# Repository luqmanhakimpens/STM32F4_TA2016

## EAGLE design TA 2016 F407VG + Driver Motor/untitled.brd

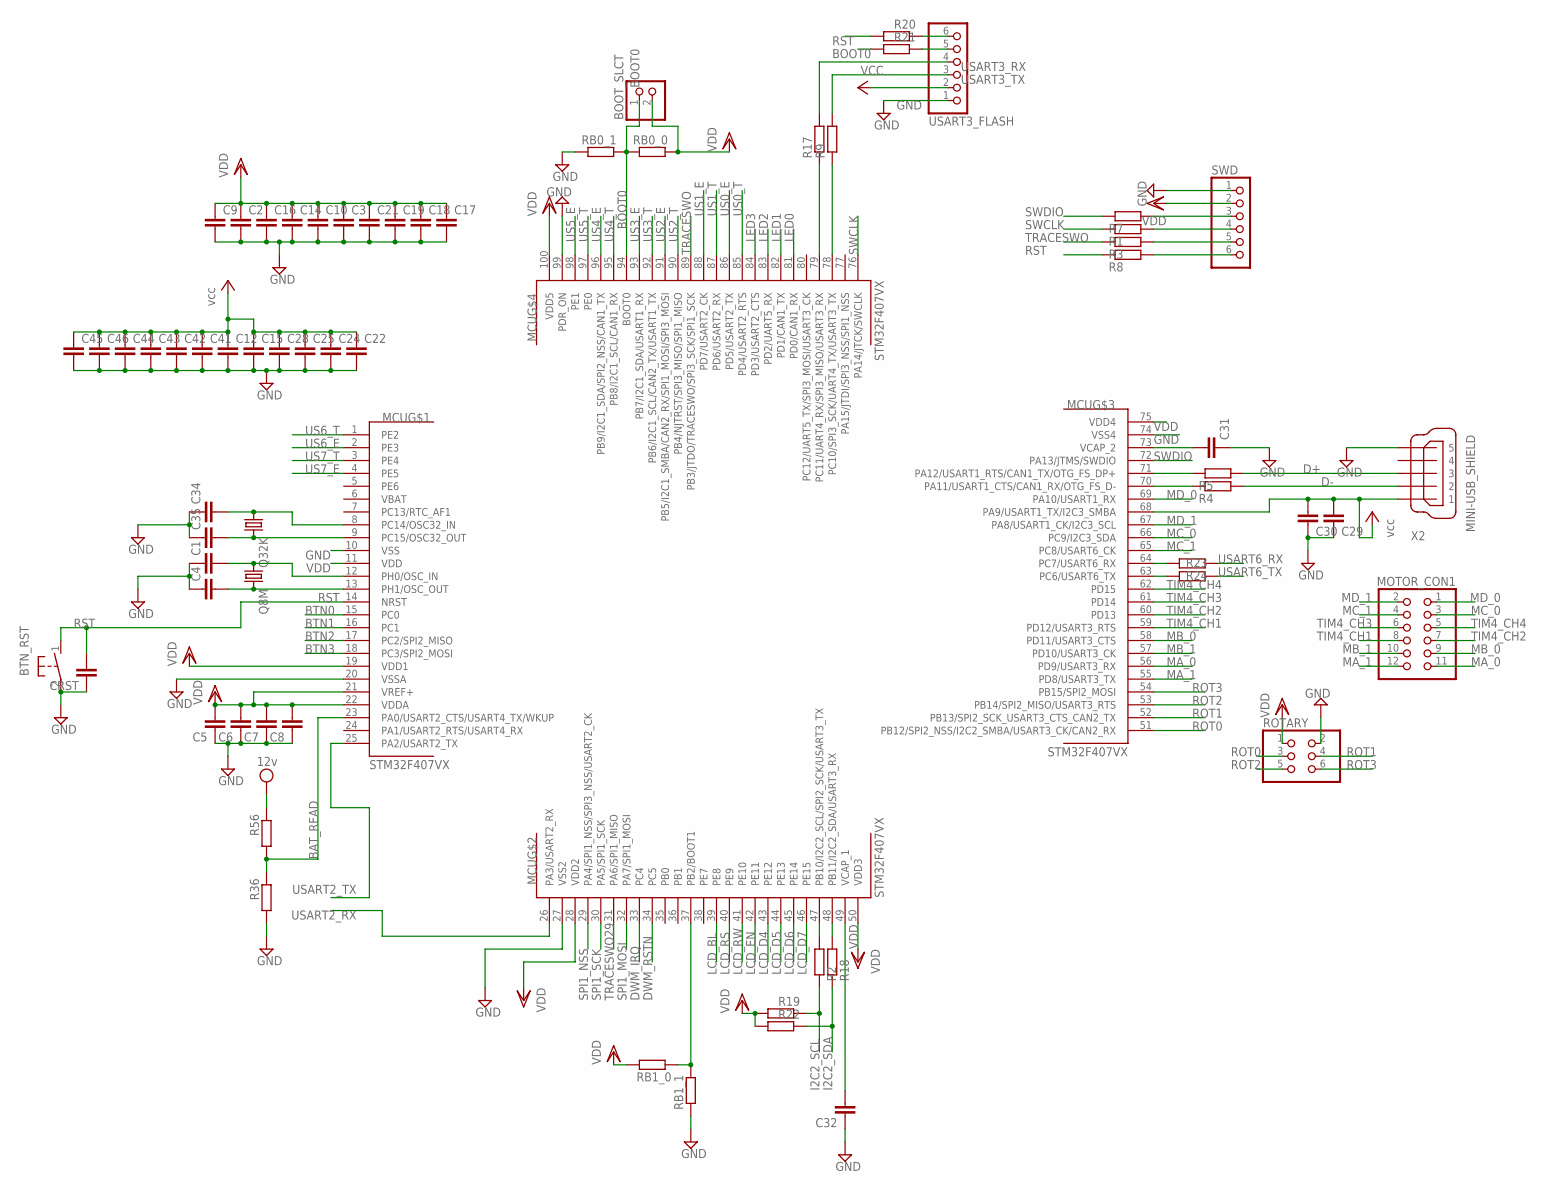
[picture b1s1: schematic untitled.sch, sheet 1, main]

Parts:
BOOT_SLCT: PINHD-1X2; 1X02
BTN_RST: PUSHBTN; PUSHBUTTON
C1, C2, C3, C4, C5, C6, C7, C8, C9, C10, C12, C14, C15, C16, C17, C18, C19, C21, C22, C24, C25, C28, C29, C30, C31, C32, C34, C35, C41, C42, C43, C44, C45, C46: C-EUC0805; C0805
CRST: C-EUC0805; C0805
MCU: STM32F407VX; LQFP100
MOTOR_CON1: PINHD-2X6; 2X06
Q8M: CRYSTALHC49U-V; HC49U-V
Q32K: CRYSTALTC26V; TC26V
R1, R2, R3, R4, R5, R7, R8, R9, R17, R18, R19, R22, R23, R24, R36, R56: R-EU_M0805; M0805
R20, R21: R-EU_R0805; R0805
RB0_0, RB0_1, RB1_0, RB1_1: R-EU_M0805; M0805
ROTARY: PINHD-2X3; 2X03
SWD: PINHD-1X06_2.54-S; 1X06-S
USART3_FLASH: PINHD-1X6; 1X06
X2: MINI-USB_SHIELD; 32005-400

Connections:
12V: R56.1; also elsewhere on the board
BAT_READ: MCU.23 (PA0/USART2_CTS/USART4_TX/WKUP), R36.1, R56.2
BOOT0: BOOT_SLCT.1, MCU.94 (BOOT0), R21.2, RB0_0.1, RB0_1.2
BOOT1: MCU.37 (PB2/BOOT1), RB1_0.1, RB1_1.2
BTN0: MCU.15 (PC0); also elsewhere on the board
BTN1: MCU.16 (PC1); also elsewhere on the board
BTN2: MCU.17 (PC2/SPI2_MISO); also elsewhere on the board
BTN3: MCU.18 (PC3/SPI2_MOSI); also elsewhere on the board
D+: R5.2, X2.3
D-: R4.2, X2.2
DWM_IRQ: MCU.33 (PC4); also elsewhere on the board
DWM_RSTN: MCU.34 (PC5); also elsewhere on the board
GND: BTN_RST.2, C1.1, C2.2, C3.2, C4.1, C5.1, C6.1, C7.1, C8.1, C9.2, C10.2, C12.2, C14.2, C15.2, C16.2, C17.2, C18.2, C19.2, C21.2, C22.2, C24.2, C25.2, C28.2, C29.1, C30.1, C31.1, C32.1, C34.1, C35.1, C41.2, C42.2, C43.2, C44.2, C45.2, C46.2, CRST.1, MCU.10 (VSS), MCU.20 (VSSA), MCU.27 (VSS2), MCU.74 (VSS4), MCU.99 (PDR_ON), R36.2, RB0_1.1, RB1_1.1, ROTARY.2, SWD.1, USART3_FLASH.1, X2.5; also elsewhere on the board
I2C2_SCL: R2.1, R19.1; also elsewhere on the board
I2C2_SDA: R18.1, R22.1; also elsewhere on the board
LCD_BL: MCU.39 (PE8); also elsewhere on the board
LCD_D4: MCU.43 (PE12); also elsewhere on the board
LCD_D5: MCU.44 (PE13); also elsewhere on the board
LCD_D6: MCU.45 (PE14); also elsewhere on the board
LCD_D7: MCU.46 (PE15); also elsewhere on the board
LCD_EN: MCU.42 (PE11); also elsewhere on the board
LCD_RS: MCU.40 (PE9); also elsewhere on the board
LCD_RW: MCU.41 (PE10); also elsewhere on the board
LED0: MCU.81 (PD0/CAN1_RX); also elsewhere on the board
LED1: MCU.82 (PD1/CAN1_TX); also elsewhere on the board
LED2: MCU.83 (PD2/UART5_RX); also elsewhere on the board
LED3: MCU.84 (PD3/USART2_CTS); also elsewhere on the board
MA_0: MCU.56 (PD9/USART3_RX), MOTOR_CON1.11
MA_1: MCU.55 (PD8/USART3_TX), MOTOR_CON1.12
MB_0: MCU.58 (PD11/USART3_CTS), MOTOR_CON1.9
MB_1: MCU.57 (PD10/USART3_CK), MOTOR_CON1.10
MC_0: MCU.66 (PC9/I2C3_SDA), MOTOR_CON1.3
MC_1: MCU.65 (PC8/USART6_CK), MOTOR_CON1.4
MD_0: MCU.69 (PA10/USART1_RX), MOTOR_CON1.1
MD_1: MCU.67 (PA8/USART1_CK/I2C3_SCL), MOTOR_CON1.2
unnamed: MCU.64 (PC7/USART6_RX), R23.1
unnamed: R3.2, SWD.5
unnamed: C31.2, MCU.73 (VCAP_2)
unnamed: MCU.63 (PC6/USART6_TX), R24.1
unnamed: R8.2, SWD.6
unnamed: R7.2, SWD.3
unnamed: R1.2, SWD.4
unnamed: MCU.47 (PB10/I2C2_SCL/SPI2_SCK/USART3_TX), R2.2
unnamed: C32.2, MCU.49 (VCAP_1)
unnamed: MCU.48 (PB11/I2C2_SDA/USART3_RX), R18.2
unnamed: R20.1, USART3_FLASH.6
unnamed: MCU.78 (PC10/SPI3_SCK/UART4_TX/USART3_TX), R9.1
unnamed: MCU.79 (PC11/UART4_RX/SPI3_MISO/USART3_RX), R17.1
unnamed: R21.1, USART3_FLASH.5
unnamed: MCU.71 (PA12/USART1_RTS/CAN1_TX/OTG_FS_DP+), R5.1
unnamed: MCU.70 (PA11/USART1_CTS/CAN1_RX/OTG_FS_D-), R4.1
OSC32_IN1: C34.2, MCU.8 (PC14/OSC32_IN), Q32K.1
OSC32_OUT1: C35.2, MCU.9 (PC15/OSC32_OUT), Q32K.2
OSC_IN: C1.2, MCU.12 (PH0/OSC_IN), Q8M.1
OSC_OUT: C4.2, MCU.13 (PH1/OSC_OUT), Q8M.2
ROT0: MCU.51 (PB12/SPI2_NSS/I2C2_SMBA/USART3_CK/CAN2_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), ROTARY.3
ROT1: MCU.52 (PB13/SPI2_SCK_USART3_CTS_CAN2_TX), ROTARY.4
ROT2: MCU.53 (PB14/SPI2_MISO/USART3_RTS), ROTARY.5
ROT3: MCU.54 (PB15/SPI2_MOSI), ROTARY.6
RST: BTN_RST.1, CRST.2, MCU.14 (NRST), R8.1, R20.2
SPI1_MOSI: MCU.32 (PA7/SPI1_MOSI); also elsewhere on the board
SPI1_NSS: MCU.29 (PA4/SPI1_NSS/SPI3_NSS/USART2_CK); also elsewhere on the board
SPI1_SCK: MCU.30 (PA5/SPI1_SCK); also elsewhere on the board
SWCLK: MCU.76 (PA14/JTCK/SWCLK), R1.1
SWDIO: MCU.72 (PA13/JTMS/SWDIO), R7.1
TIM4_CH1: MCU.59 (PD12/USART3_RTS), MOTOR_CON1.8
TIM4_CH2: MCU.60 (PD13), MOTOR_CON1.7
TIM4_CH3: MCU.61 (PD14), MOTOR_CON1.6
TIM4_CH4: MCU.62 (PD15), MOTOR_CON1.5
TRACESWO: MCU.89 (PB3/JTDO/TRACESWO/SPI3_SCK/SPI1_SCK), R3.1
TRACESWO29: MCU.31 (PA6/SPI1_MISO); also elsewhere on the board
US0_E: MCU.86 (PD5/USART2_TX); also elsewhere on the board
US0_T: MCU.85 (PD4/USART2_RTS); also elsewhere on the board
US1_E: MCU.88 (PD7/USART2_CK); also elsewhere on the board
US1_T: MCU.87 (PD6/USART2_RX); also elsewhere on the board
US2_E: MCU.91 (PB5/I2C1_SMBA/CAN2_RX/SPI1_MOSI/SPI3_MO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); also elsewhere on the board
US2_T: MCU.90 (PB4/NJTRST/SPI3_MISO/SPI1_MISO); also elsewhere on the board
US3_E: MCU.93 (PB7/I2C1_SDA/USART1_RX); also elsewhere on the board
US3_T: MCU.92 (PB6/I2C1_SCL/CAN2_TX/USART1_TX); also elsewhere on the board
US4_E: MCU.96 (PB9/I2C1_SDA/SPI2_NSS/CAN1_TX); also elsewhere on the board
US4_T: MCU.95 (PB8/I2C1_SCL/CAN1_RX); also elsewhere on the board
US5_E: MCU.98 (PE1); also elsewhere on the board
US5_T: MCU.97 (PE0); also elsewhere on the board
US6_E: MCU.2 (PE3); also elsewhere on the board
US6_T: MCU.1 (PE2); also elsewhere on the board
US7_E: MCU.4 (PE5); also elsewhere on the board
US7_T: MCU.3 (PE4); also elsewhere on the board
USART2_RX: MCU.26 (PA3/USART2_RX); also elsewhere on the board
USART2_TX: MCU.25 (PA2/USART2_TX); also elsewhere on the board
USART3_RX: R17.2, USART3_FLASH.4; also elsewhere on the board
USART3_TX: R9.2, USART3_FLASH.3; also elsewhere on the board
USART6_RX: R23.2; also elsewhere on the board
USART6_TX: R24.2; also elsewhere on the board
VCC: C12.1, C15.1, C22.1, C24.1, C25.1, C28.1, C29.2, C30.2, C41.1, C42.1, C43.1, C44.1, C45.1, C46.1, MCU.68 (PA9/USART1_TX/I2C3_SMBA), USART3_FLASH.2, X2.1; also elsewhere on the board
VDD: BOOT_SLCT.2, C2.1, C3.1, C5.2, C6.2, C7.2, C8.2, C9.1, C10.1, C14.1, C16.1, C17.1, C18.1, C19.1, C21.1, MCU.11 (VDD), MCU.19 (VDD1), MCU.21 (VREF+), MCU.22 (VDDA), MCU.28 (VDD2), MCU.50 (VDD3), MCU.75 (VDD4), MCU.100 (VDD5), R19.2, R22.2, RB0_0.2, RB1_0.2, ROTARY.1, SWD.2; also elsewhere on the board

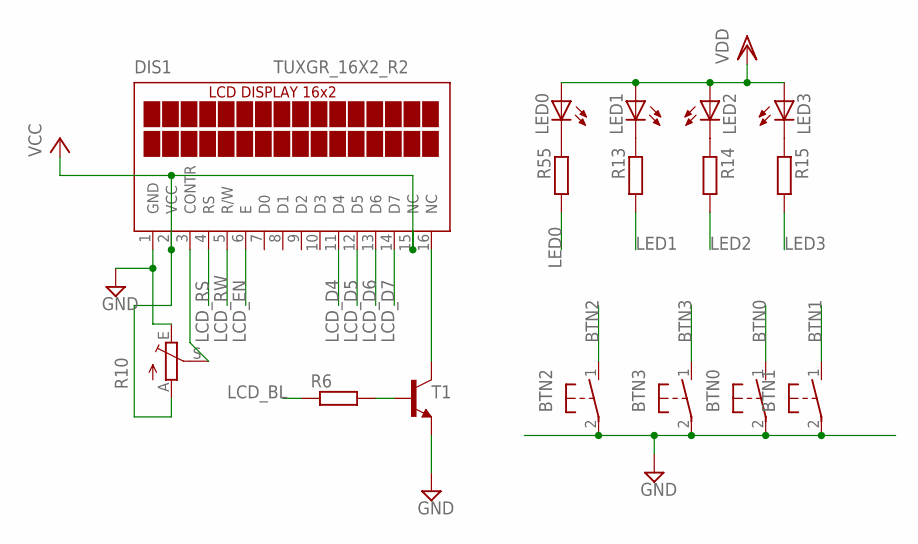
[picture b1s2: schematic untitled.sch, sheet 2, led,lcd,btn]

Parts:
BTN0, BTN1, BTN2, BTN3: PUSHBTN; PUSHBUTTON
DIS1: TUXGR_16X2_R2
LED0, LED1, LED2, LED3: LEDSMT1206; 1206
R6, R13, R14, R15, R55: R-EU_M0805; M0805
R10: TRIM_EU-CA6V; CA6V
T1: BC818-NPN-SOT23-BEC; SOT23-BEC

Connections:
BTN0: BTN0.1; also elsewhere on the board
BTN1: BTN1.1; also elsewhere on the board
BTN2: BTN2.1; also elsewhere on the board
BTN3: BTN3.1; also elsewhere on the board
GND: BTN0.2, BTN1.2, BTN2.2, BTN3.2, DIS1.1 (GND), R10.E, T1.E; also elsewhere on the board
LCD_BL: R6.1; also elsewhere on the board
LCD_D4: DIS1.11 (D4); also elsewhere on the board
LCD_D5: DIS1.12 (D5); also elsewhere on the board
LCD_D6: DIS1.13 (D6); also elsewhere on the board
LCD_D7: DIS1.14 (D7); also elsewhere on the board
LCD_EN: DIS1.6 (E); also elsewhere on the board
LCD_RS: DIS1.4 (RS); also elsewhere on the board
LCD_RW: DIS1.5 (R/W); also elsewhere on the board
LED0: R55.2; also elsewhere on the board
LED1: R13.2; also elsewhere on the board
LED2: R14.2; also elsewhere on the board
LED3: R15.2; also elsewhere on the board
unnamed: DIS1.3 (CONTR), R10.S
unnamed: LED1.C, R13.1
unnamed: LED2.C, R14.1
unnamed: LED3.C, R15.1
unnamed: R6.2, T1.B
unnamed: DIS1.16 (NC), T1.C
unnamed: LED0.C, R55.1
VCC: DIS1.2 (VCC), DIS1.15 (NC), R10.A; also elsewhere on the board
VDD: LED0.A, LED1.A, LED2.A, LED3.A; also elsewhere on the board

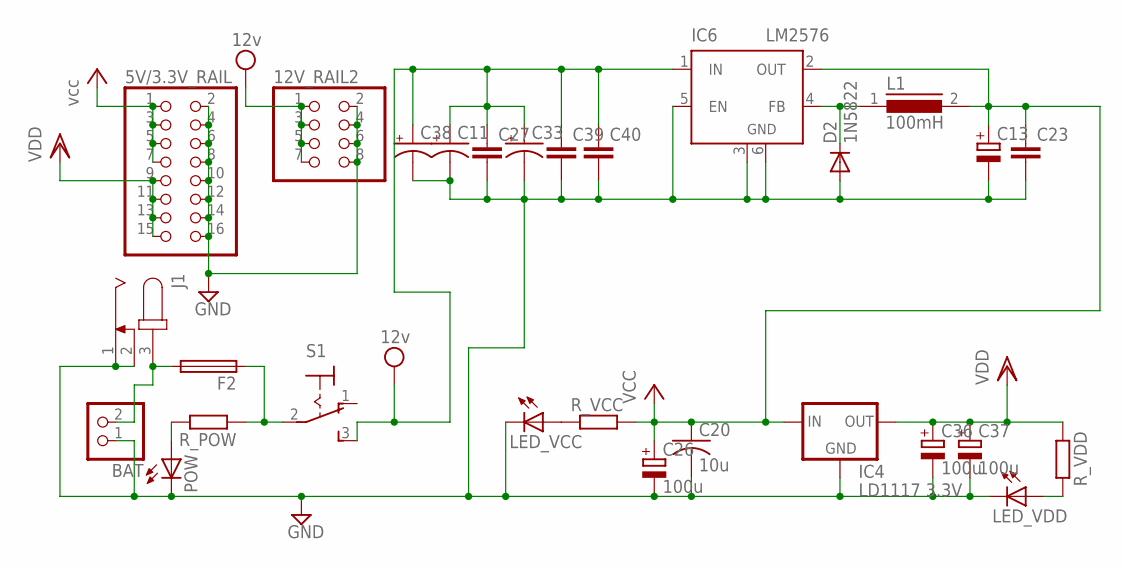
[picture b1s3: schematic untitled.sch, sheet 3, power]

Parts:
5V/3.3V_RAIL: PINHD-2X8; 2X08
12V_RAIL2: PINHD-2X4; 2X04
BAT: PINHD-1X2; 1X02
C11, C33, C38: CAP_POLH13; PANASONIC_H13
C13: CPOL-EU153CLV-1012; 153CLV-1012
C20: 10u; C0805
C23, C27, C39, C40: C-EUC0805; C0805
C26, C36, C37: 100u; 153CLV-1012
D2: 1N5822; DO15-12
F2: FUSESHK20L; SHK20L
IC4: LD1117 3.3V; SOT223
IC6: LM2576; TO263-5
J1: JACK-PLUG1; SPC4078
L1: 100mH; DR127
LED_VCC: LEDSMT1206; 1206
LED_VDD: LEDSMT1206; 1206
POW: LEDSMT1206; 1206
R_POW: R-EU_M0805; M0805
R_VCC: R-EU_M0805; M0805
R_VDD: R-EU_M0805; M0805
S1: 320-916

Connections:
12V: 12V_RAIL2.1, 12V_RAIL2.3, 12V_RAIL2.5, 12V_RAIL2.7, C11.+, C27.1, C33.+, C38.+, C39.1, C40.1, IC6.1 (IN), S1.3 (S); also elsewhere on the board
GND: 5V/3.3V_RAIL.2, 5V/3.3V_RAIL.4, 5V/3.3V_RAIL.6, 5V/3.3V_RAIL.8, 5V/3.3V_RAIL.10, 5V/3.3V_RAIL.12, 5V/3.3V_RAIL.14, 5V/3.3V_RAIL.16, 12V_RAIL2.2, 12V_RAIL2.4, 12V_RAIL2.6, 12V_RAIL2.8, BAT.1, C11.-, C13.-, C20.2, C23.2, C26.-, C27.2, C33.-, C36.-, C37.-, C38.-, C39.2, C40.2, D2.A, IC4.1 (GND), IC6.3 (GND), IC6.5 (EN), IC6.6 (GND), J1.1, J1.2, LED_VCC.C, LED_VDD.C, POW.C; also elsewhere on the board
unnamed: BAT.2, F2.2A (2), J1.3
unnamed: LED_VDD.A, R_VDD.2
unnamed: D2.C, IC6.4 (FB), L1.1
unnamed: POW.A, R_POW.2
unnamed: LED_VCC.A, R_VCC.1
unnamed: F2.1A (1), R_POW.1, S1.2
VCC: 5V/3.3V_RAIL.1, 5V/3.3V_RAIL.3, 5V/3.3V_RAIL.5, 5V/3.3V_RAIL.7, C13.+, C20.1, C23.1, C26.+, IC4.3 (IN), IC6.2 (OUT), L1.2, R_VCC.2; also elsewhere on the board
VDD: 5V/3.3V_RAIL.9, 5V/3.3V_RAIL.11, 5V/3.3V_RAIL.13, 5V/3.3V_RAIL.15, C36.+, C37.+, IC4.2 (OUT), R_VDD.1; also elsewhere on the board

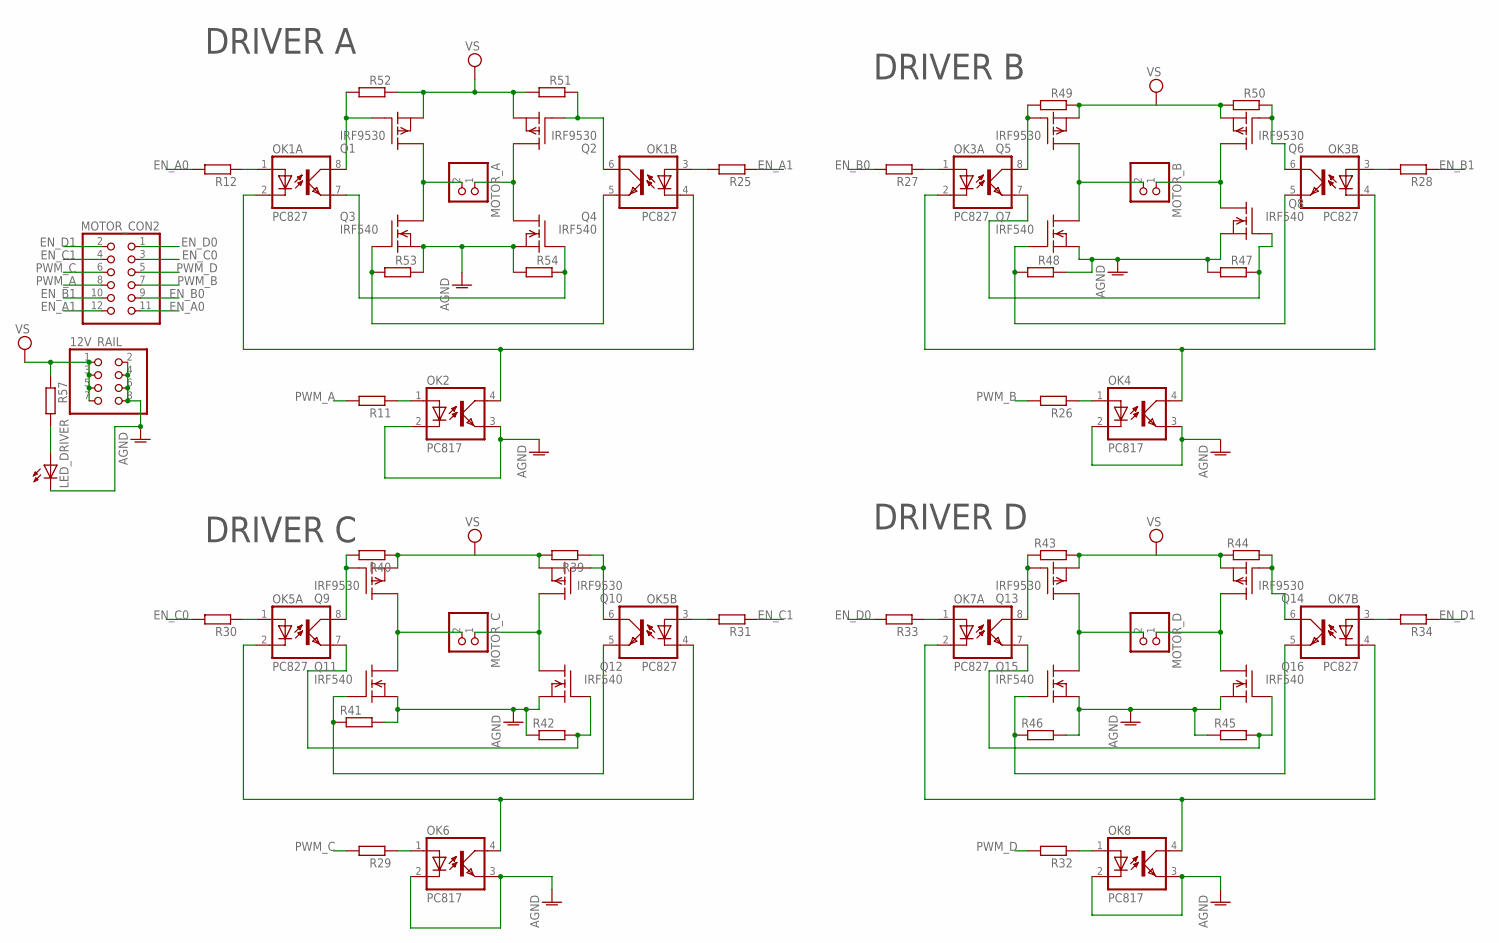
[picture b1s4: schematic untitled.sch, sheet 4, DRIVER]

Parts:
12V_RAIL: PINHD-2X4; 2X04
LED_DRIVER: LEDSMT1206; 1206
MOTOR_A: PINHD-1X2/90; 1X02/90
MOTOR_B: PINHD-1X2/90; 1X02/90
MOTOR_C: PINHD-1X2/90; 1X02/90
MOTOR_CON2: PINHD-2X6; 2X06
MOTOR_D: PINHD-1X2/90; 1X02/90
OK1, OK3, OK5, OK7: PC827; DIL08
OK2, OK4, OK6, OK8: PC817; DIL04
Q1, Q2, Q5, Q6, Q9, Q10, Q13, Q14: IRF9530; TO220
Q3, Q4, Q7, Q8, Q11, Q12, Q15, Q16: IRF540; TO220
R11, R12, R25, R26, R27, R28, R29, R30, R31, R32, R33, R34, R39, R40, R41, R42, R43, R44, R45, R46, R47, R48, R49, R50, R51, R52, R53, R54, R57: R-EU_M0805; M0805

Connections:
AGND: 12V_RAIL.2, 12V_RAIL.4, 12V_RAIL.6, 12V_RAIL.8, LED_DRIVER.C, OK2.2 (C), OK2.3 (EMIT), OK4.2 (C), OK4.3 (EMIT), OK6.2 (C), OK6.3 (EMIT), OK8.2 (C), OK8.3 (EMIT), Q3.3 (S), Q4.3 (S), Q7.3 (S), Q8.3 (S), Q11.3 (S), Q12.3 (S), Q15.3 (S), Q16.3 (S), R41.2, R42.1, R45.1, R46.2, R47.2, R48.1, R53.1, R54.2
EN_A0: MOTOR_CON2.11, R12.2
EN_A1: MOTOR_CON2.12, R25.1
EN_B0: MOTOR_CON2.9, R27.2
EN_B1: MOTOR_CON2.10, R28.1
EN_C0: MOTOR_CON2.3, R30.2
EN_C1: MOTOR_CON2.4, R31.1
EN_D0: MOTOR_CON2.1, R33.2
EN_D1: MOTOR_CON2.2, R34.1
unnamed: OK3.7 (EMIT), Q8.1 (G), R47.1
unnamed: MOTOR_A.2, Q1.2 (D), Q3.2 (D)
unnamed: MOTOR_A.1, Q2.2 (D), Q4.2 (D)
unnamed: OK1.8 (COL), Q1.1 (G), R52.2
unnamed: OK1.7 (EMIT), Q4.1 (G), R54.1
unnamed: OK1.6 (COL), Q2.1 (G), R51.1
unnamed: OK1.5 (EMIT), Q3.1 (G), R53.2
unnamed: OK1.2 (C), OK1.4 (C), OK2.4 (COL)
unnamed: MOTOR_B.2, Q5.2 (D), Q7.2 (D)
unnamed: MOTOR_B.1, Q6.2 (D), Q8.2 (D)
unnamed: OK1.1 (A), R12.1
unnamed: OK1.3 (A), R25.2
unnamed: OK3.8 (COL), Q5.1 (G), R49.2
unnamed: OK2.1 (A), R11.1
unnamed: OK3.6 (COL), Q6.1 (G), R50.1
unnamed: OK3.5 (EMIT), Q7.1 (G), R48.2
unnamed: OK3.2 (C), OK3.4 (C), OK4.4 (COL)
unnamed: OK3.1 (A), R27.1
unnamed: OK3.3 (A), R28.2
unnamed: OK4.1 (A), R26.1
unnamed: MOTOR_C.2, Q9.2 (D), Q11.2 (D)
unnamed: MOTOR_C.1, Q10.2 (D), Q12.2 (D)
unnamed: OK5.8 (COL), Q9.1 (G), R40.2
unnamed: OK5.7 (EMIT), Q12.1 (G), R42.2
unnamed: OK5.6 (COL), Q10.1 (G), R39.1
unnamed: OK5.5 (EMIT), Q11.1 (G), R41.1
unnamed: OK5.2 (C), OK5.4 (C), OK6.4 (COL)
unnamed: OK5.1 (A), R30.1
unnamed: OK5.3 (A), R31.2
unnamed: OK6.1 (A), R29.1
unnamed: MOTOR_D.2, Q13.2 (D), Q15.2 (D)
unnamed: MOTOR_D.1, Q14.2 (D), Q16.2 (D)
unnamed: OK7.8 (COL), Q13.1 (G), R43.1
unnamed: OK7.7 (EMIT), Q16.1 (G), R45.2
unnamed: OK7.6 (COL), Q14.1 (G), R44.2
unnamed: OK7.5 (EMIT), Q15.1 (G), R46.1
unnamed: OK7.2 (C), OK7.4 (C), OK8.4 (COL)
unnamed: OK7.1 (A), R33.1
unnamed: OK7.3 (A), R34.2
unnamed: OK8.1 (A), R32.1
unnamed: LED_DRIVER.A, R57.2
PWM_A: MOTOR_CON2.8, R11.2
PWM_B: MOTOR_CON2.7, R26.2
PWM_C: MOTOR_CON2.6, R29.2
PWM_D: MOTOR_CON2.5, R32.2
VS+: 12V_RAIL.1, 12V_RAIL.3, 12V_RAIL.5, 12V_RAIL.7, Q1.3 (S), Q2.3 (S), Q5.3 (S), Q6.3 (S), Q9.3 (S), Q10.3 (S), Q13.3 (S), Q14.3 (S), R39.2, R40.1, R43.2, R44.1, R49.1, R50.2, R51.2, R52.1, R57.1

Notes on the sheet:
DRIVER A
DRIVER B
DRIVER C
DRIVER D

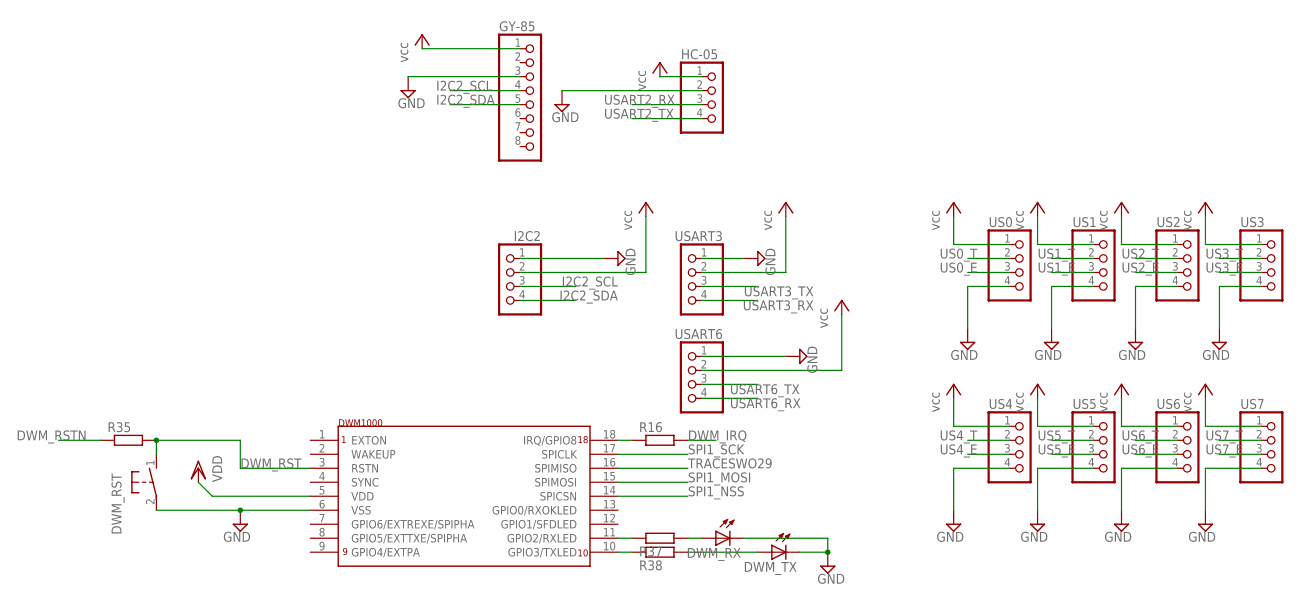
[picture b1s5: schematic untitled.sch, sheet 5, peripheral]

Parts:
DWM_RST: PUSHBTN; PUSHBUTTON
DWM_RX: LEDSMT1206; 1206
DWM_TX: LEDSMT1206; 1206
GY-85: PINHD-1X8; 1X08
HC-05: PINHD-1X4; 1X04
I2C2: PINHD-1X4; 1X04
R16, R35, R37, R38: R-EU_M0805; M0805
U$3: MY_DWM1000_PAD_ONLY
US0, US1, US2, US3, US4, US5, US6, US7: PINHD-1X4; 1X04
USART3, USART6: PINHD-1X4; 1X04

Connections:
DWM_IRQ: R16.2; also elsewhere on the board
DWM_RST: DWM_RST.1, R35.2, U$3.3 (RSTN)
DWM_RSTN: R35.1; also elsewhere on the board
GND: DWM_RST.2, DWM_RX.C, DWM_TX.C, GY-85.3, HC-05.2, I2C2.1, U$3.6 (VSS), US0.4, US1.4, US2.4, US3.4, US4.4, US5.4, US6.4, US7.4, USART3.1, USART6.1; also elsewhere on the board
I2C2_SCL: GY-85.4, I2C2.3; also elsewhere on the board
I2C2_SDA: GY-85.5, I2C2.4; also elsewhere on the board
unnamed: R37.1, U$3.11 (GPIO2/RXLED)
unnamed: R38.1, U$3.10 (GPIO3/TXLED)
unnamed: DWM_RX.A, R37.2
unnamed: DWM_TX.A, R38.2
unnamed: R16.1, U$3.18 (IRQ/GPIO8)
SPI1_MOSI: U$3.15 (SPIMOSI); also elsewhere on the board
SPI1_NSS: U$3.14 (SPICSN); also elsewhere on the board
SPI1_SCK: U$3.17 (SPICLK); also elsewhere on the board
TRACESWO29: U$3.16 (SPIMISO); also elsewhere on the board
US0_E: US0.3; also elsewhere on the board
US0_T: US0.2; also elsewhere on the board
US1_E: US1.3; also elsewhere on the board
US1_T: US1.2; also elsewhere on the board
US2_E: US2.3; also elsewhere on the board
US2_T: US2.2; also elsewhere on the board
US3_E: US3.3; also elsewhere on the board
US3_T: US3.2; also elsewhere on the board
US4_E: US4.3; also elsewhere on the board
US4_T: US4.2; also elsewhere on the board
US5_E: US5.3; also elsewhere on the board
US5_T: US5.2; also elsewhere on the board
US6_E: US6.3; also elsewhere on the board
US6_T: US6.2; also elsewhere on the board
US7_E: US7.3; also elsewhere on the board
US7_T: US7.2; also elsewhere on the board
USART2_RX: HC-05.3; also elsewhere on the board
USART2_TX: HC-05.4; also elsewhere on the board
USART3_RX: USART3.4; also elsewhere on the board
USART3_TX: USART3.3; also elsewhere on the board
USART6_RX: USART6.4; also elsewhere on the board
USART6_TX: USART6.3; also elsewhere on the board
VCC: GY-85.1, HC-05.1, I2C2.2, US0.1, US1.1, US2.1, US3.1, US4.1, US5.1, US6.1, US7.1, USART3.2, USART6.2; also elsewhere on the board
VDD: U$3.5 (VDD); also elsewhere on the board

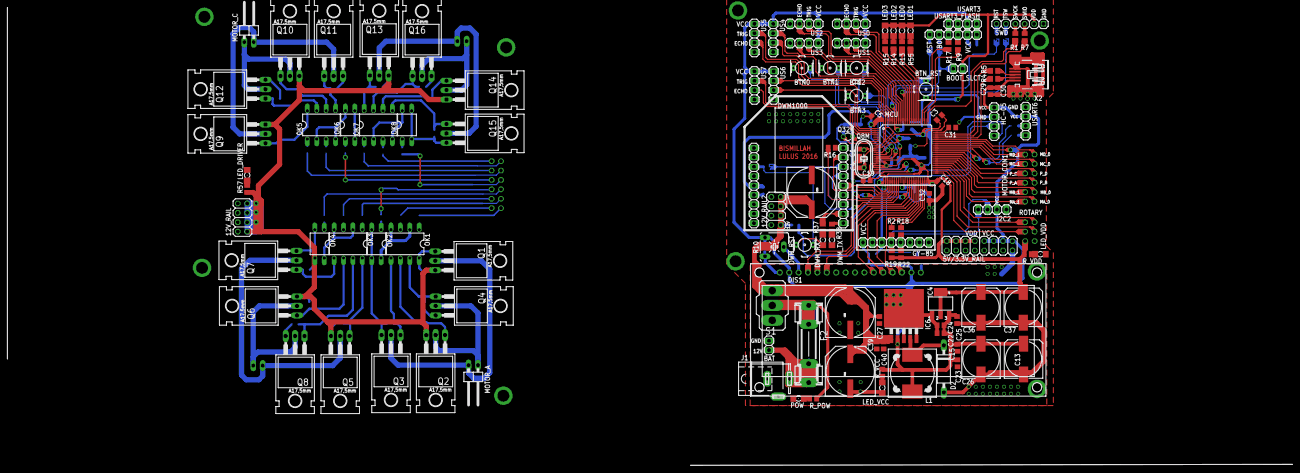
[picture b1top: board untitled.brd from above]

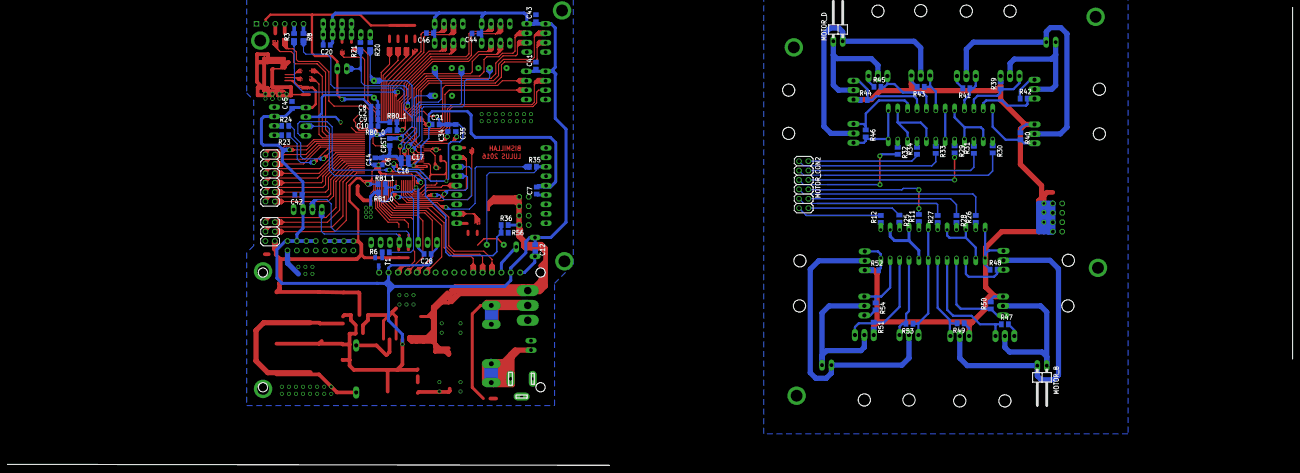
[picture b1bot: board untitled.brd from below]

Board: 2 copper layers, 347.2 x 123.7 mm, 192 parts (70 on the bottom side), 169 nets.

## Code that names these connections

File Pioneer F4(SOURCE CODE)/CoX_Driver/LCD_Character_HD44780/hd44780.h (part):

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//! @{
//
//*****************************************************************************    
#define HD44780_PIN_D7          PA7
#define HD44780_PIN_D6          PA6
#define HD44780_PIN_D5          PA5
#define HD44780_PIN_D4          PA4
#define HD44780_PIN_D3          PA3
#define HD44780_PIN_D2          PA2
#define HD44780_PIN_D1          PA1
#define HD44780_PIN_D0          PA0

#define HD44780_PIN_E           PE0
#define HD44780_PIN_RW          PE1
#define HD44780_PIN_RS          PE2
//*****************************************************************************
//
//! @}
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
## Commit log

2018-07-04 FINAL-PROJECT_EEPIS_2016
    Final project PENS(EEPIS) 2016: "Path Planning Based on Indoor Positioning System for Mobile Robot"
2018-07-04 FINAL-PROJECT_EEPIS_2016
    delete unnecesary file and rename folders
2018-07-04 rename folder pcb

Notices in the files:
Pioneer F4(SOURCE CODE)/CoX_Driver/LCD_Character_HD44780/hd44780.h:
Copyright (c)  2011, CooCoX
All rights reserved.
parts and their libraries:
STM32F407Vx_LQFP100: Copyright 2012 by Ersan Günes, Quantitec, info@quantitec.de
SparkFun-Passives: Licensing: CC v3.0 Share-Alike You are welcome to use this library for commercial purposes.
